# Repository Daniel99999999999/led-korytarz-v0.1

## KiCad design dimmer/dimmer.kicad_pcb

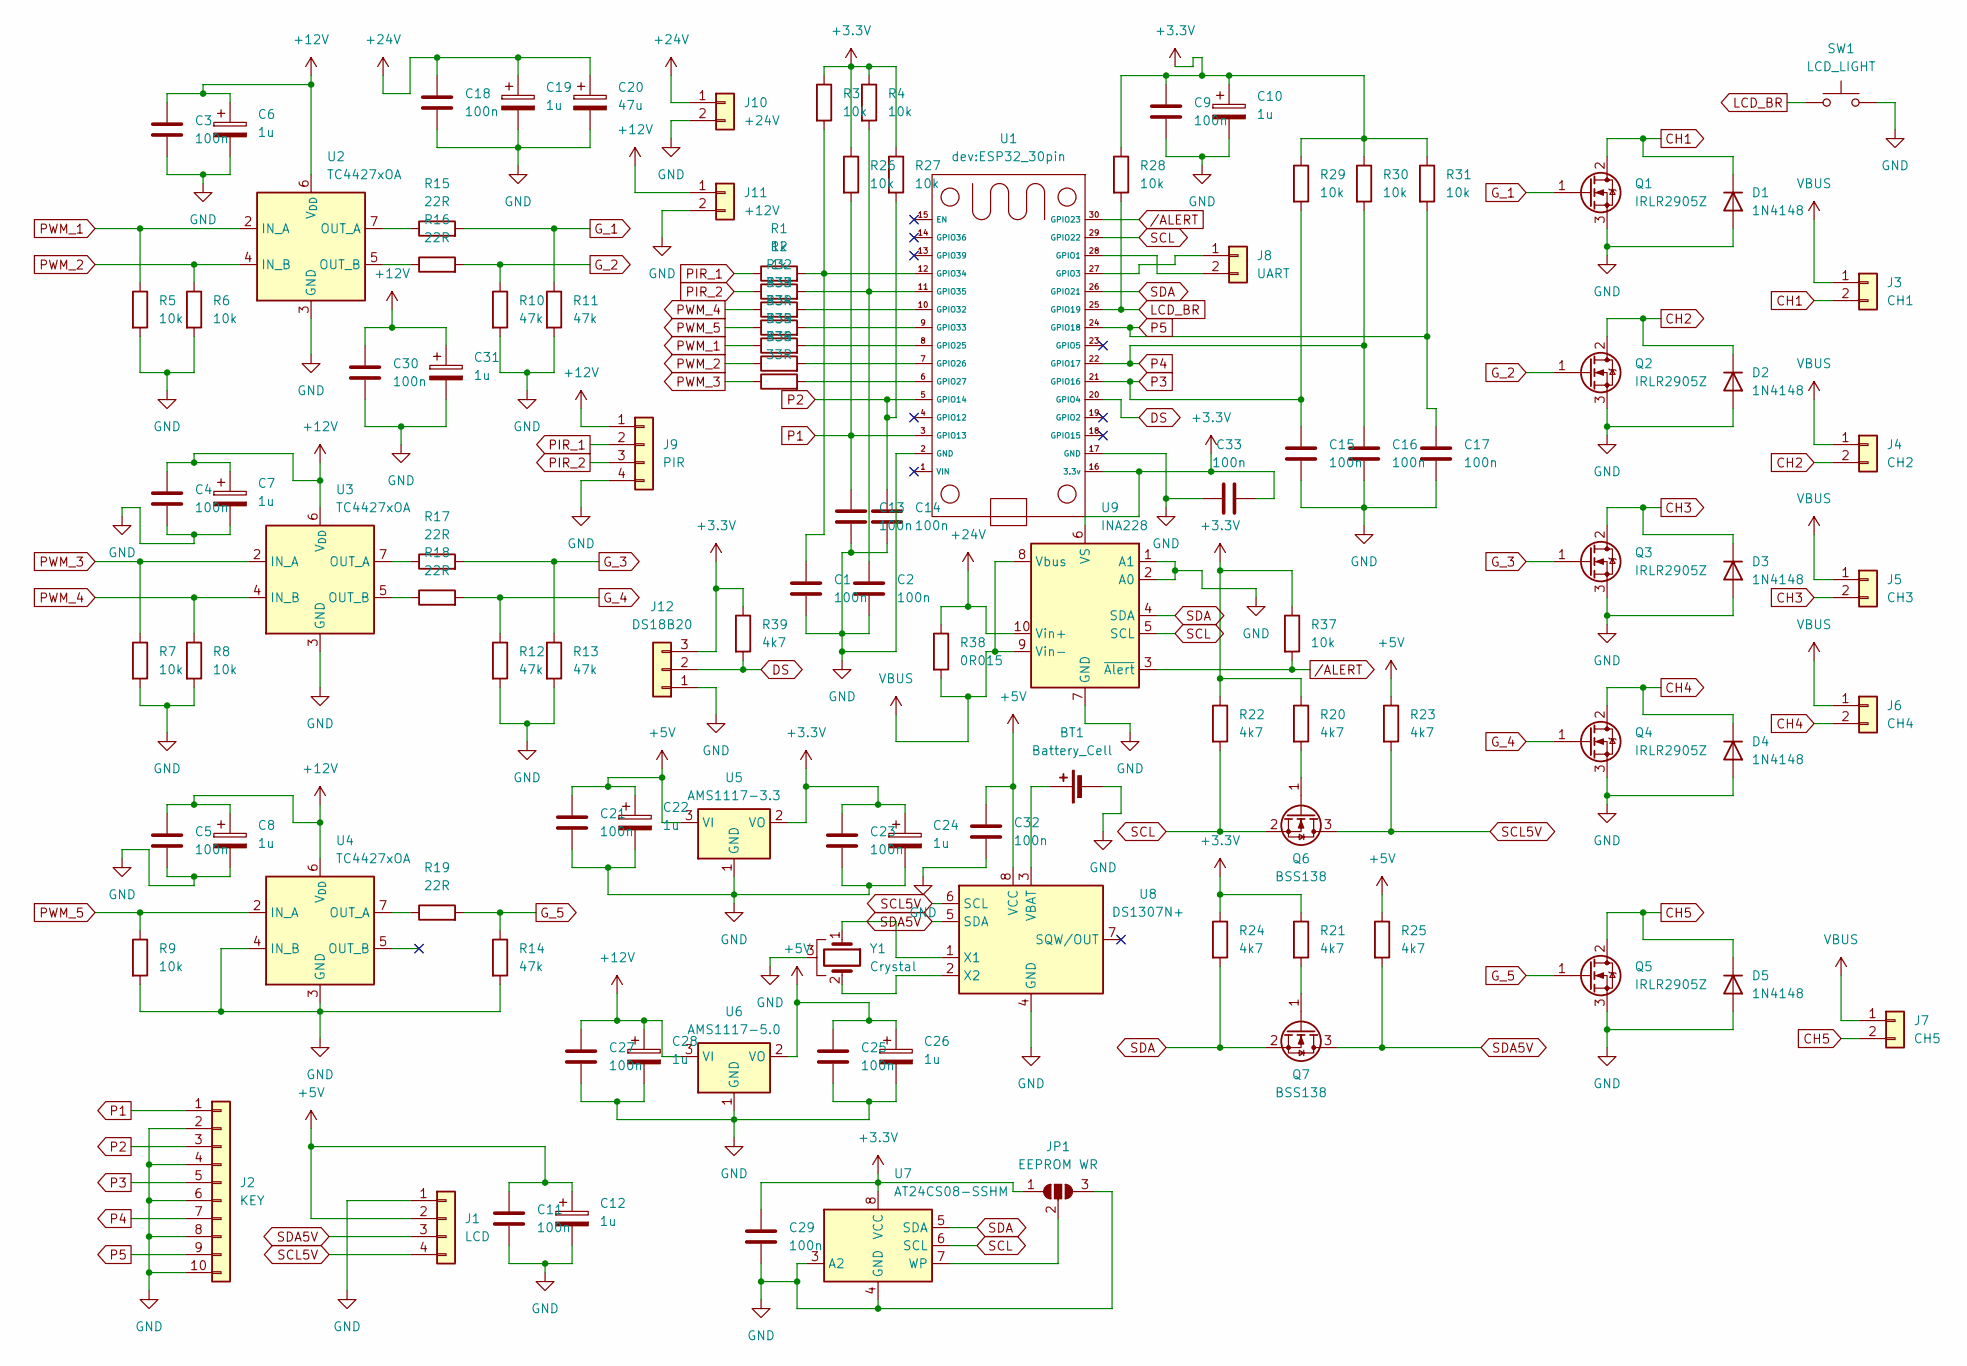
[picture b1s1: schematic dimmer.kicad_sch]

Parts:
BT1: Battery_Cell; Battery_Panasonic_CR2032-HFN_Horizontal_CircularHoles
C1, C2, C3, C4, C5, C9, C11, C13, C14, C15, C16, C17, C18, C21, C23, C25, C27, C29, C30, C32, C33: 100n; C_0805_2012Metric
C6, C7, C8, C10, C12, C19, C22, C24, C26, C28, C31: 1u; CP_EIA-1608-08_AVX-J
C20: 47u; CP_Elec_6.3x5.4_Nichicon
D1, D2, D3, D4, D5: 1N4148; D_MELF_Handsoldering
J1: LCD; PinHeader_1x04_P2.54mm_Vertical
J2: KEY; PhoenixContact_MCV_1,5_10-G-3.5_1x10_P3.50mm_Vertical
J3: CH1; PhoenixContact_MCV_1,5_2-G-3.5_1x02_P3.50mm_Vertical
J4: CH2; PhoenixContact_MCV_1,5_2-G-3.5_1x02_P3.50mm_Vertical
J5: CH3; PhoenixContact_MCV_1,5_2-G-3.5_1x02_P3.50mm_Vertical
J6: CH4; PhoenixContact_MCV_1,5_2-G-3.5_1x02_P3.50mm_Vertical
J7: CH5; PhoenixContact_MCV_1,5_2-G-3.5_1x02_P3.50mm_Vertical
J8: UART; PhoenixContact_MCV_1,5_2-G-3.5_1x02_P3.50mm_Vertical
J9: PIR; PhoenixContact_MCV_1,5_4-G-3.5_1x04_P3.50mm_Vertical
J10: +24V; TerminalBlock_Phoenix_MKDS-1,5-2-5.08_1x02_P5.08mm_Horizont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
J11: +12V; TerminalBlock_Phoenix_MKDS-1,5-2-5.08_1x02_P5.08mm_Horizont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
J12: DS18B20; Molex_KK-254_AE-6410-03A_1x03_P2.54mm_Vertical
JP1: EEPROM WR; SolderJumper-3_P2.0mm_Open_TrianglePad1.0x1.5mm
Q1, Q2, Q3, Q4, Q5: IRLR2905Z; TO-252-2
Q6, Q7: BSS138; SOT-23
R1, R2: 1k; R_0805_2012Metric
R3, R4, R5, R6, R7, R8, R9, R26, R27, R28, R29, R30, R31, R37: 10k; R_0805_2012Metric
R10, R11, R12, R13, R14: 47k; R_0805_2012Metric
R15, R16, R17, R18, R19: 22R; R_0805_2012Metric
R20, R21, R22, R23, R24, R25, R39: 4k7; R_0805_2012Metric
R32, R33, R34, R35, R36: 33R; R_0805_2012Metric
R38: 0R015; R_2512_6332Metric_Pad1.40x3.35mm_HandSolder
SW1: LCD_LIGHT; SW_Push_1P1T_NO_CK_KSC7xxJ
U1: ESP32_30pin
U2, U3, U4: TC4427xOA; SOIC-8_3.9x4.9mm_P1.27mm
U5: AMS1117-3.3; SOT-223-3_TabPin2
U6: AMS1117-5.0; SOT-223-3_TabPin2
U7: AT24CS08-SSHM; SOIC-8_3.9x4.9mm_P1.27mm
U8: DS1307N+; DIP-8_W7.62mm
U9: INA228; TSSOP-10_3x3mm_P0.5mm
Y1: Crystal; Crystal_AT310_D3.0mm_L10.0mm_Horizontal_1EP_style1

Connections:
+3.3V: C9.1, C10.1, C23.1, C24.1, C29.1, C33.2, J12.3, JP1.1 (A), R3.1, R4.1, R20.1, R21.1, R22.1, R24.1, R26.1, R27.1, R28.1, R29.1, R30.1, R31.1, R37.1, R39.1, U1.16 (3.3v), U5.2 (VO), U7.8 (VCC), U9.6 (VS)
+5V: C11.1, C12.1, C21.1, C22.1, C25.1, C26.1, C32.1, J1.2, R23.1, R25.1, U5.3 (VI), U6.2 (VO), U8.8 (VCC)
+12V: C3.1, C4.1, C5.1, C6.1, C7.1, C8.1, C27.1, C28.1, C30.1, C31.1, J9.1, J11.1, U2.6 (V_{DD}), U3.6 (V_{DD}), U4.6 (V_{DD}), U6.3 (VI)
+24V: C18.1, C19.1, C20.1, J10.1, R38.1, U9.10 (Vin+)
CH1: D1.1 (K), J3.2, Q1.2 (D)
CH2: D2.1 (K), J4.2, Q2.2 (D)
CH3: D3.1 (K), J5.2, Q3.2 (D)
CH4: D4.1 (K), J6.2, Q4.2 (D)
CH5: D5.1 (K), J7.2, Q5.2 (D)
DS: J12.2, R39.2, U1.20 (GPIO4)
GND: BT1.2 (-), C1.2, C2.2, C3.2, C4.2, C5.2, C6.2, C7.2, C8.2, C9.2, C10.2, C11.2, C12.2, C13.2, C14.2, C15.2, C16.2, C17.2, C18.2, C19.2, C20.2, C21.2, C22.2, C23.2, C24.2, C25.2, C26.2, C27.2, C28.2, C29.2, C30.2, C31.2, C32.2, C33.1, D1.2 (A), D2.2 (A), D3.2 (A), D4.2 (A), D5.2 (A), J1.1, J2.2, J2.4, J2.6, J2.8, J2.10, J9.4, J10.2, J11.2, J12.1, JP1.3 (B), Q1.3 (S), Q2.3 (S), Q3.3 (S), Q4.3 (S), Q5.3 (S), R5.2, R6.2, R7.2, R8.2, R9.2, R10.2, R11.2, R12.2, R13.2, R14.2, SW1.2, U1.2 (GND), U1.17 (GND), U2.3 (GND), U3.3 (GND), U4.3 (GND), U4.4 (IN_B), U5.1 (GND), U6.1 (GND), U7.3 (A2), U7.4 (GND), U8.4 (GND), U9.1 (A1), U9.2 (A0), U9.7 (GND), Y1.3
G_1: Q1.1 (G), R11.1, R15.2
G_2: Q2.1 (G), R10.1, R16.2
G_3: Q3.1 (G), R13.1, R17.2
G_4: Q4.1 (G), R12.1, R18.2
G_5: Q5.1 (G), R14.1, R19.2
LCD_BR: R28.2, SW1.1, U1.25 (GPIO19)
unnamed: BT1.1 (+), U8.3 (VBAT)
unnamed: J8.1, U1.27 (GPIO3)
unnamed: J8.2, U1.28 (GPIO1)
unnamed: JP1.2 (C), U7.7 (WP)
unnamed: Q6.1 (G), R20.2
unnamed: Q7.1 (G), R21.2
unnamed: R34.2, U1.8 (GPIO25)
unnamed: R35.2, U1.7 (GPIO26)
unnamed: R36.2, U1.6 (GPIO27)
unnamed: R32.2, U1.10 (GPIO32)
unnamed: R33.2, U1.9 (GPIO33)
unnamed: C1.1, R1.2, R3.2, U1.12 (GPIO34)
unnamed: C2.1, R2.2, R4.2, U1.11 (GPIO35)
unnamed: R15.1, U2.7 (OUT_A)
unnamed: R16.1, U2.5 (OUT_B)
unnamed: R17.1, U3.7 (OUT_A)
unnamed: R18.1, U3.5 (OUT_B)
unnamed: R19.1, U4.7 (OUT_A)
unnamed: U8.1 (X1), Y1.1
unnamed: U8.2 (X2), Y1.2
P1: C13.1, J2.1, R26.2, U1.3 (GPIO13)
P2: C14.1, J2.3, R27.2, U1.5 (GPIO14)
P3: C15.1, J2.5, R29.2, U1.21 (GPIO16)
P4: C16.1, J2.7, R30.2, U1.22 (GPIO17)
P5: C17.1, J2.9, R31.2, U1.24 (GPIO18)
PIR_1: J9.2, R1.1
PIR_2: J9.3, R2.1
PWM_1: R5.1, R34.1, U2.2 (IN_A)
PWM_2: R6.1, R35.1, U2.4 (IN_B)
PWM_3: R7.1, R36.1, U3.2 (IN_A)
PWM_4: R8.1, R32.1, U3.4 (IN_B)
PWM_5: R9.1, R33.1, U4.2 (IN_A)
SCL: Q6.2 (S), R22.2, U1.29 (GPIO22), U7.6 (SCL), U9.5 (SCL)
SCL5V: J1.4, Q6.3 (D), R23.2, U8.6 (SCL)
SDA: Q7.2 (S), R24.2, U1.26 (GPIO21), U7.5 (SDA), U9.4 (SDA)
SDA5V: J1.3, Q7.3 (D), R25.2, U8.5 (SDA)
VBUS: J3.1, J4.1, J5.1, J6.1, J7.1, R38.2, U9.8 (Vbus), U9.9 (Vin-)
/ALERT: R37.2, U1.30 (GPIO23), U9.3 (~Alert)

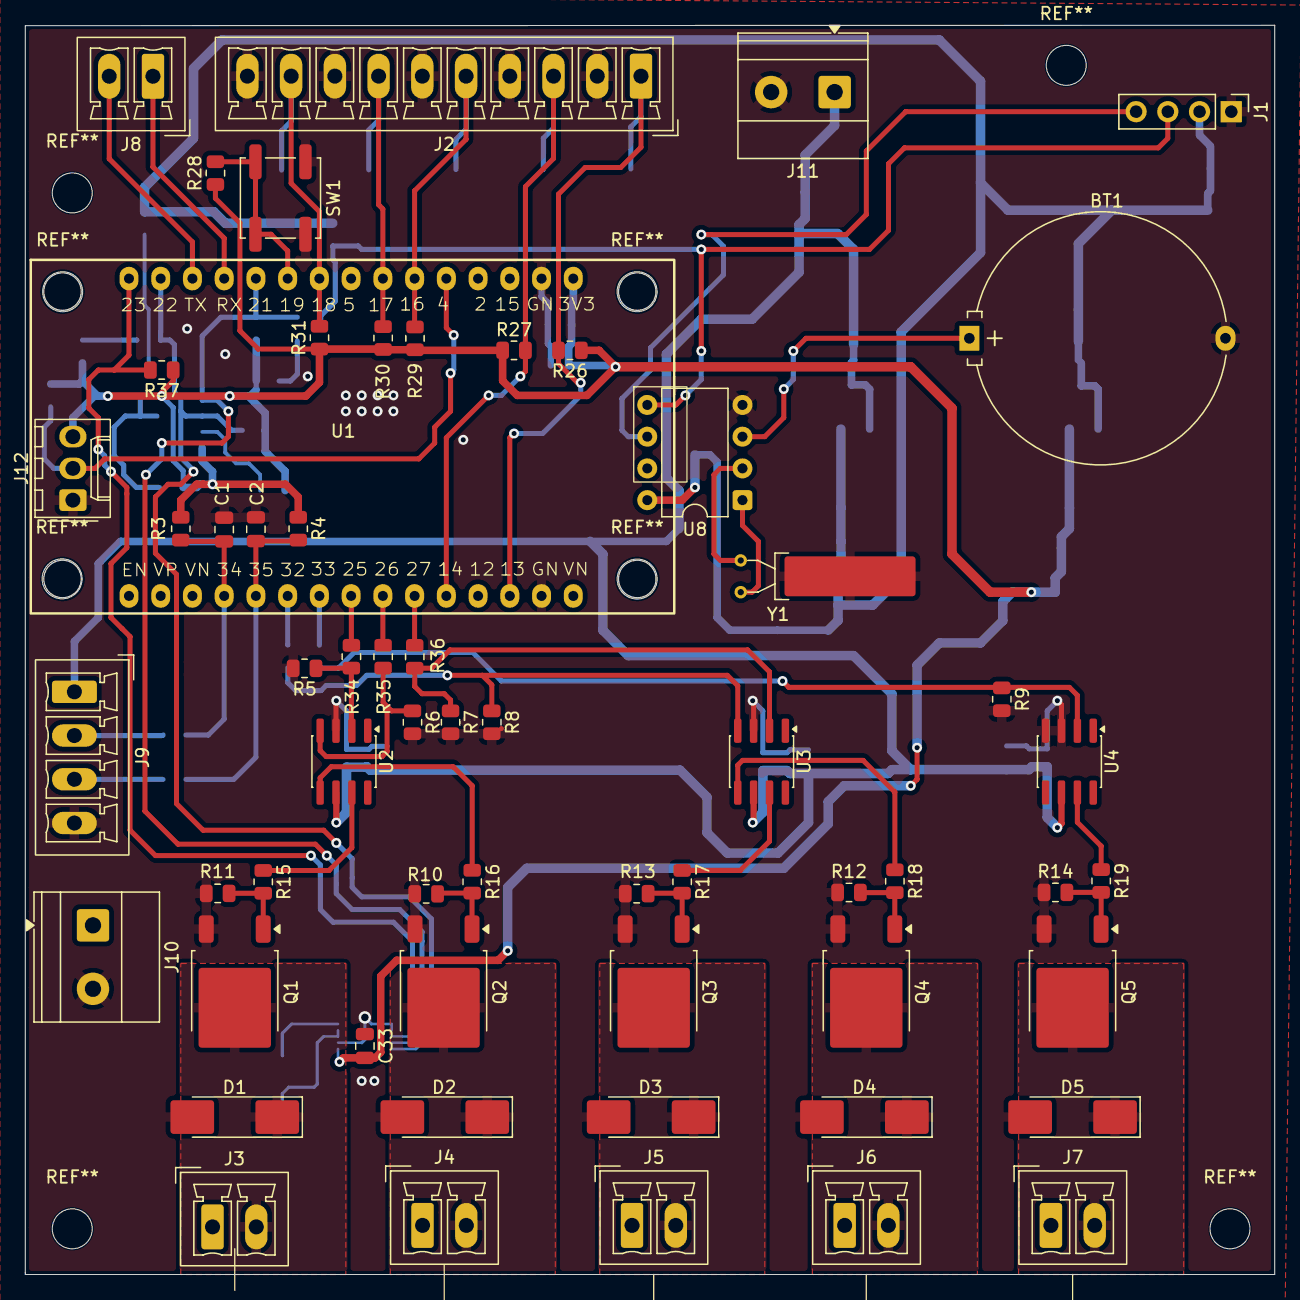
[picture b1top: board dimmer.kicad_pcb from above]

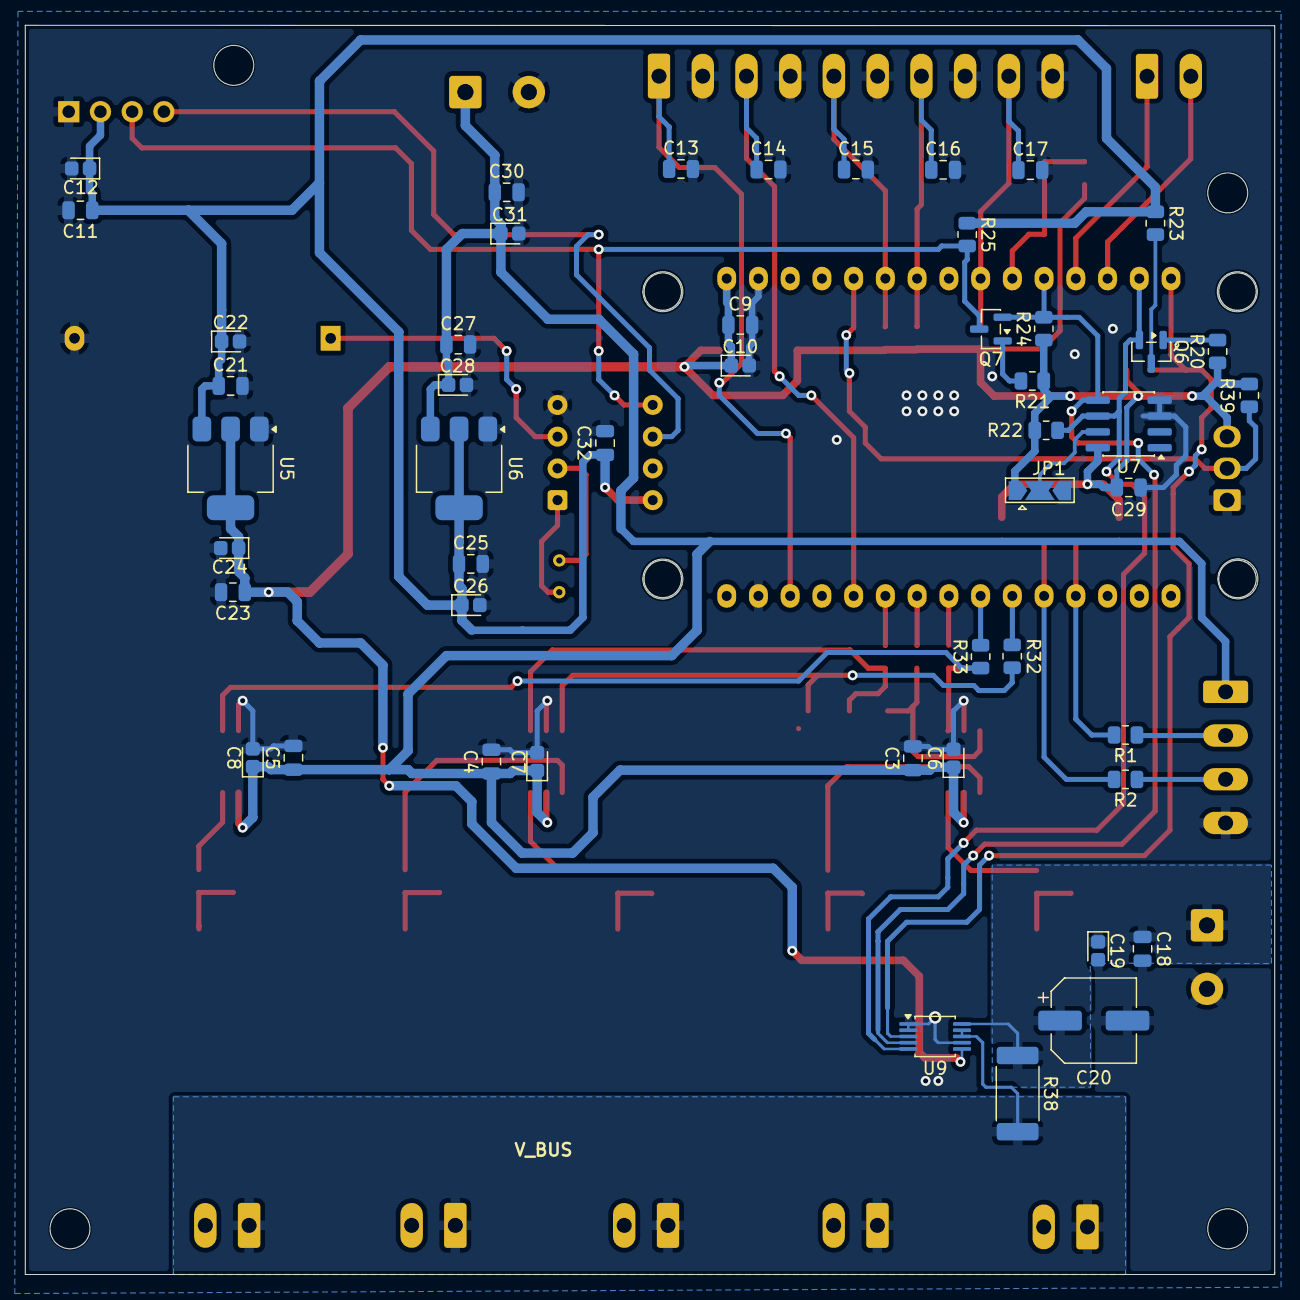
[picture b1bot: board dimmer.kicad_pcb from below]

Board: 2 copper layers, 100.0 x 100.0 mm, 109 parts (49 on the bottom side), 55 nets.
